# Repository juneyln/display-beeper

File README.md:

# display-beeper
the thing from limbus company

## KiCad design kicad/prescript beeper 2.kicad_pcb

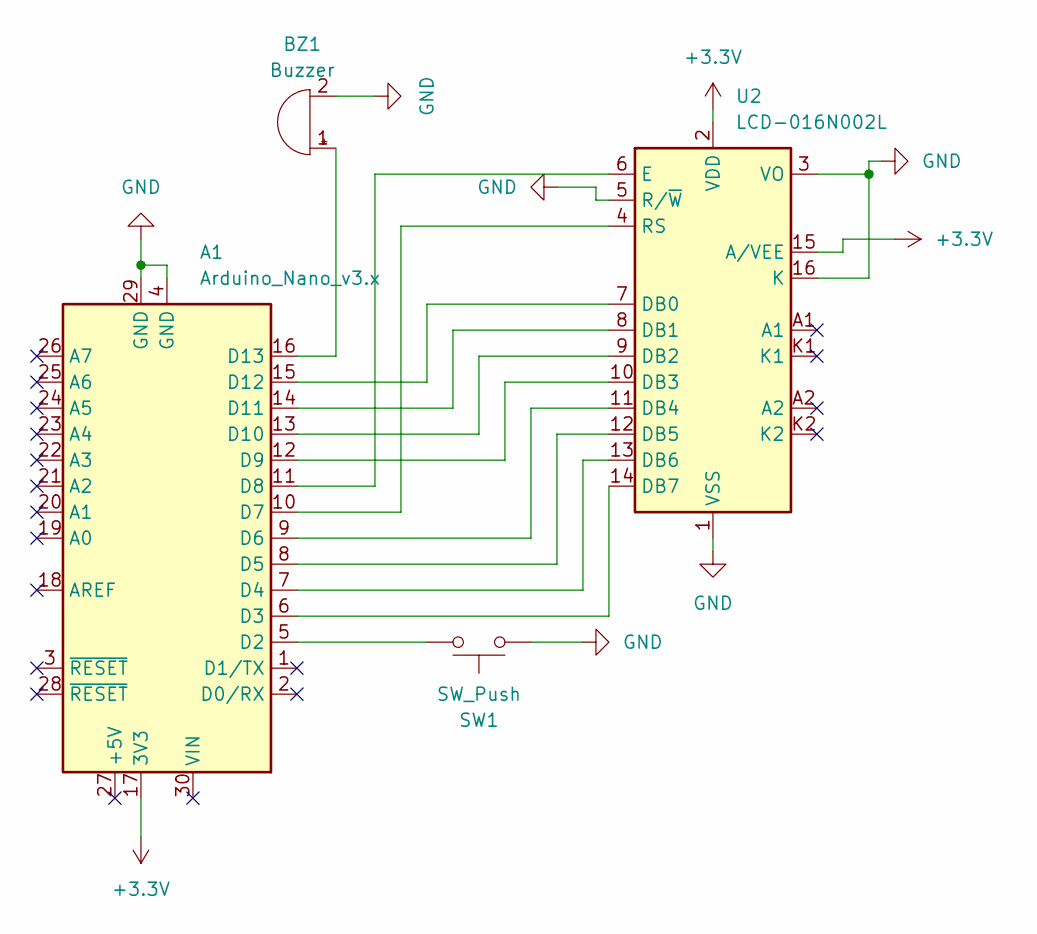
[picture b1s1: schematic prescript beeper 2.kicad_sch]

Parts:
A1: Arduino_Nano_v3.x; Arduino_Nano
BZ1: Buzzer; PS1720P02
SW1: SW_Push; SW_PUSH_6mm
U2: LCD-016N002L; NHD-0216K1Z-NSW-BBW-L

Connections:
+3.3V: A1.17 (3V3), U2.2 (VDD), U2.15 (A/VEE)
GND: A1.4 (GND), A1.29 (GND), BZ1.2 (-), SW1.1, U2.1 (VSS), U2.3 (VO), U2.5 (R/~W), U2.16 (K)
unnamed: A1.5 (D2), SW1.2
unnamed: A1.6 (D3), U2.14 (DB7)
unnamed: A1.7 (D4), U2.13 (DB6)
unnamed: A1.8 (D5), U2.12 (DB5)
unnamed: A1.9 (D6), U2.11 (DB4)
unnamed: A1.10 (D7), U2.4 (RS)
unnamed: A1.11 (D8), U2.6 (E)
unnamed: A1.12 (D9), U2.10 (DB3)
unnamed: A1.13 (D10), U2.9 (DB2)
unnamed: A1.14 (D11), U2.8 (DB1)
unnamed: A1.15 (D12), U2.7 (DB0)
unnamed: A1.16 (D13), BZ1.1 (+)

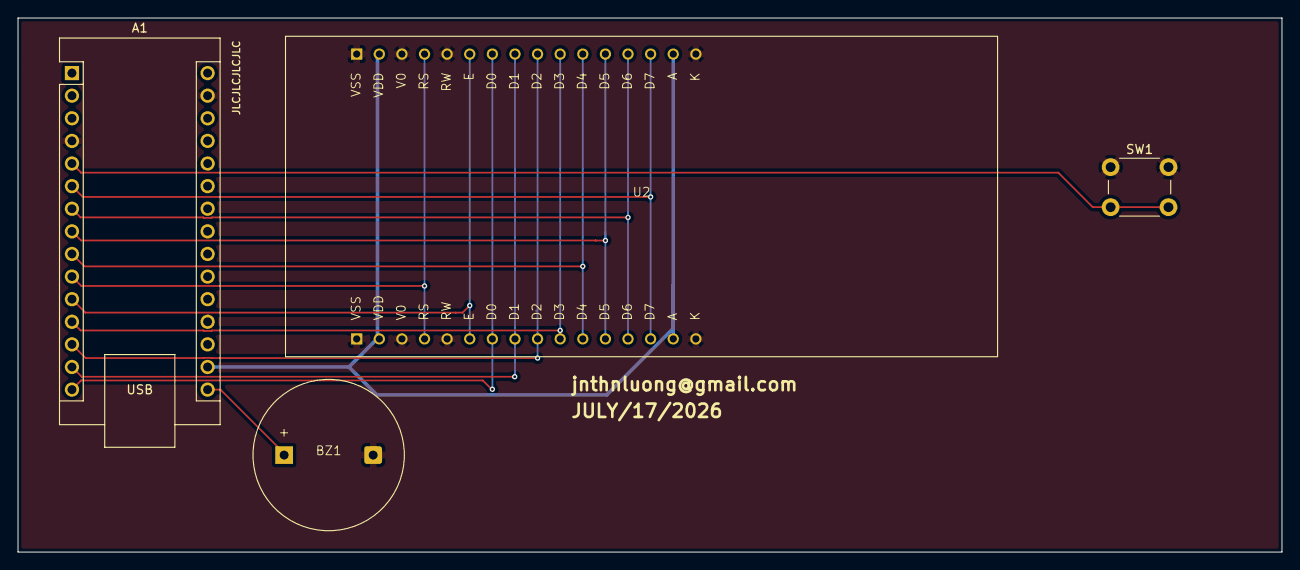
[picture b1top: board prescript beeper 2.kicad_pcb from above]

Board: 4 copper layers, 142.0 x 60.0 mm, 4 parts (0 on the bottom side), 14 nets.
